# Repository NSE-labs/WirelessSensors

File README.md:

# WirelessSensors
 Development of wireless sensor hardware and software.

 Links to more information:

 [Project Overview](./Documentation/Wireless%20Sensor%20Project.md)

 [Project Checklist](./Documentation/Tasks.md)

 [CPU Board Rev A.1 Debugging](./Documentation/CPU%20board%20rev%20A.1%20debugging.md)

 [LoRa Board Rev A.1 Debugging](./Documentation/LoRa%20board%20rev%20A.1%20debugging.md)

 [LoRa Gateway Development](./Documentation/LoRa%20gateway%20development.md)

 [Range Testing](./Documentation/Range%20testing.md)

 [Sensor Module Architecture](./Documentation/Sensor%20module%20architecture.md)

 [CPU Board Rev B.2](./Documentation/CPU%20board%20rev%20B.2.md)

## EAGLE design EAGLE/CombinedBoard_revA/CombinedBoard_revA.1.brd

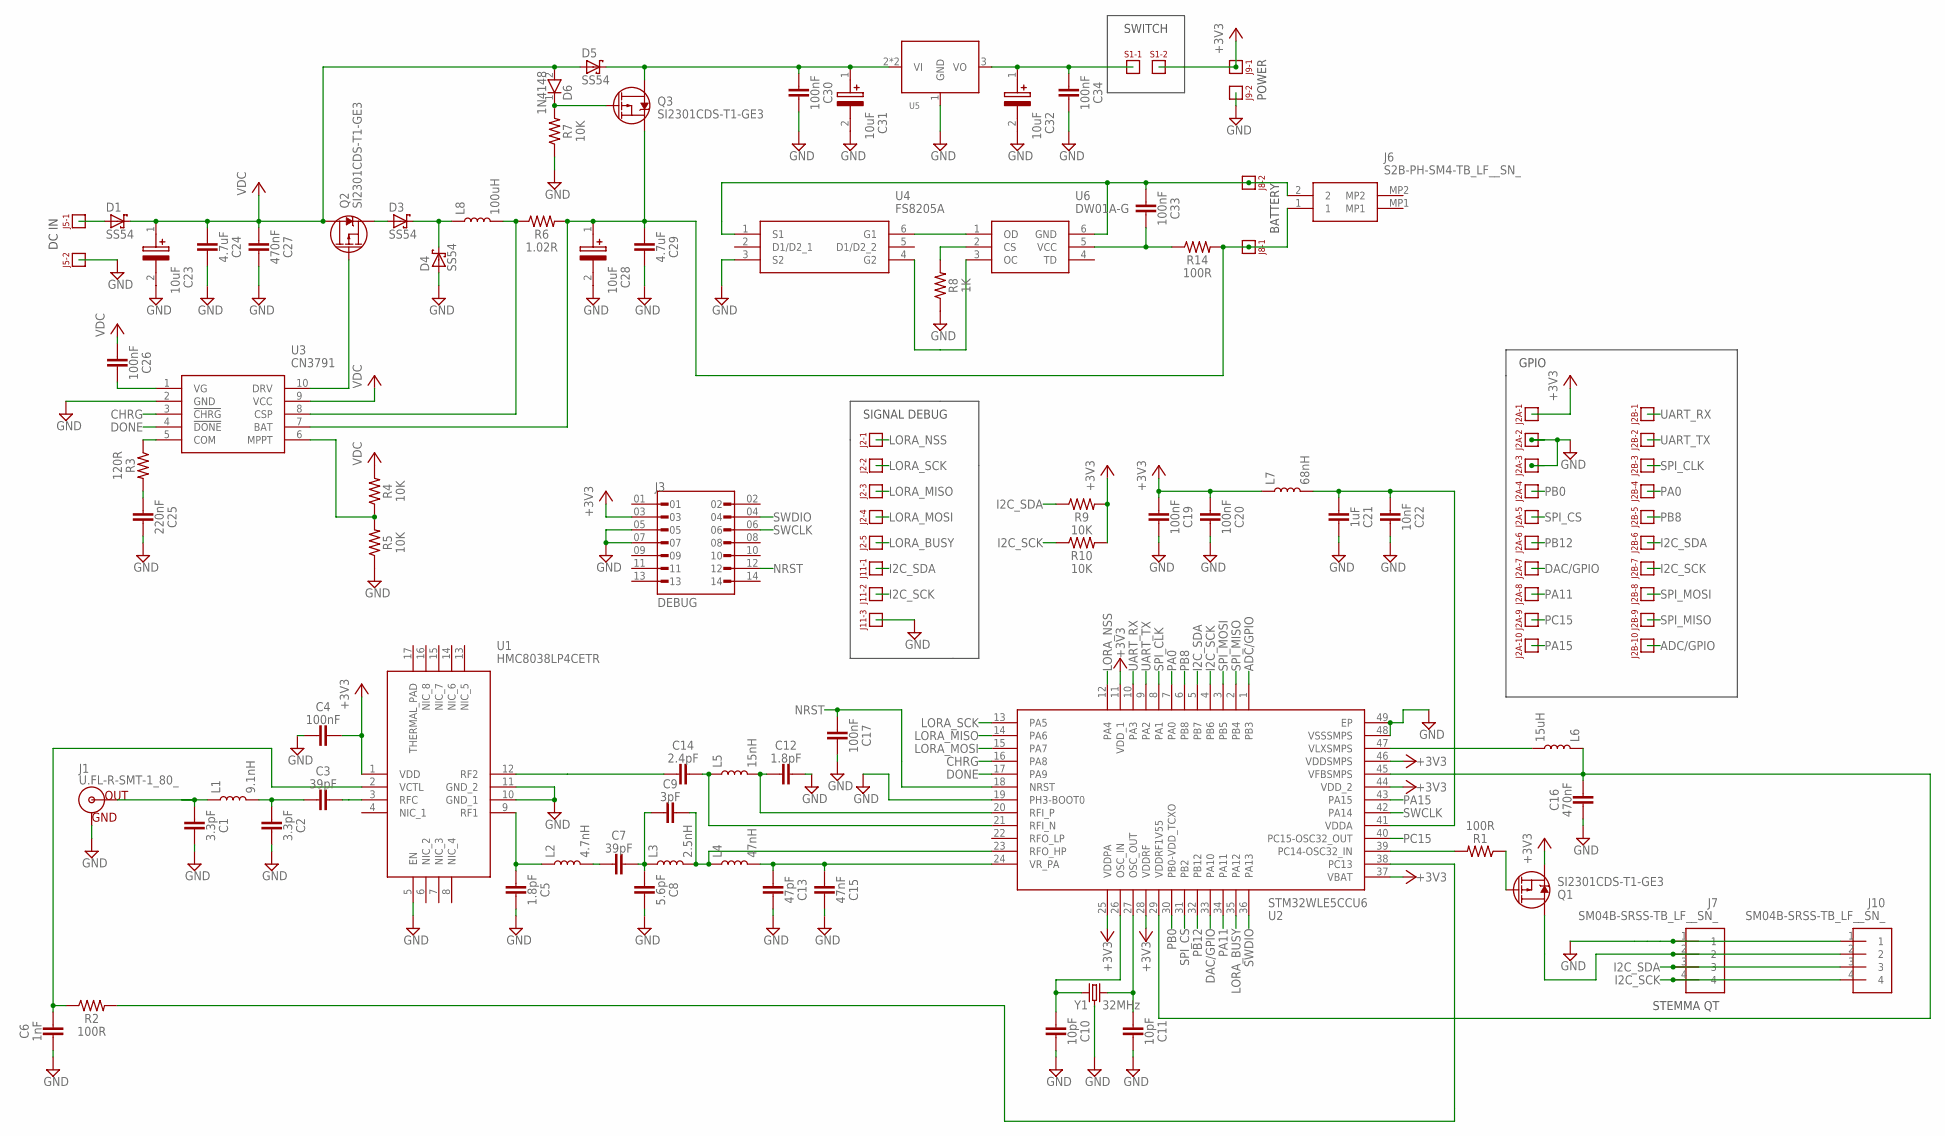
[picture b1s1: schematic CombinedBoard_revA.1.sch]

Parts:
C1, C2: 3.3pF; 0402
C3, C7: 39pF; 0402
C4, C17, C19, C20, C26, C30, C33, C34: 100nF; 0402
C5, C12: 1.8pF; 0402
C6: 1nF; 0603
C8: 5.6pF; 0402
C9: 3pF; 0603
C10, C11: 10pF; 0402
C13: 47pF; 0603
C14: 2.4pF; 0402
C15: 47nF; 0603
C16: 470nF; 0402
C21: 1uF; 0402
C22: 10nF; 0402
C23, C28, C31, C32: 10uF; 4MM_SMD_ECAP
C24, C29: 4.7uF; 1206
C25: 220nF; 0603
C27: 470nF; 0805
D1, D3, D4, D5: SS54; SMA(DO-214AC)
D6: 1N4148; SOD3716X135N
J1: U.FL-R-SMT-1_80_; UFLRSMT180
J2: HEADER_5PIN
J2A, J2B: HEADER_10PIN
J3: DEBUG; HEADER_DEBUG_SMD
J5: SOLAR; HEADER_2PIN
J6: S2B-PH-SM4-TB_LF__SN_; S2BPHSM4TBLFSN
J7, J10: SM04B-SRSS-TB_LF__SN_; SM04B-SRSS-TB(LFSN)
J8: BATTERY; HEADER_2PIN
J9: POWER; HEADER_2PIN
J11: HEADER_3PIN
L1: 9.1nH; 0402
L2: 4.7nH; 0402
L3: 2.5nH; 0402
L4: 47nH; 0603
L5: 15nH; 0402
L6: 15uH; 0805
L7: 68nH; 0603
L8: 100uH; L_SMD,7X7.8MM
Q1, Q2, Q3: SI2301CDS-T1-GE3; SOT-23
R1, R2, R14: 100R; 0402
R3: 120R; 0805
R4, R5, R7, R9, R10: 10K; 0402
R6: 1.02R; 1206
R8: 1K; 0402
S1: HEADER_2PIN
U1: HMC8038LP4CETR; QFN65P400X400X90-17N
U2: STM32WLE5CCU6; QFN50P700X700X60-49N
U3: CN3791; SOP100P600X175-10N
U4: FS8205A; SOT95P280X125-6N
U5: LDO_SOT89; SOT-89-3
U6: DW01A-G; SOT95P280X135-6N
Y1: 32MHz; SMD2016-4P

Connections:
+3V3: C4.2, C19.1, C20.1, J2A.P$1, J3.03, J9.P$1, L7.1, Q1.3 (S), R9.2, R10.2, S1.P$2, U1.1 (VDD), U2.11 (VDD_1), U2.25 (VDDPA), U2.28 (VDDRF), U2.37 (VBAT), U2.44 (VDD_2), U2.46 (VDDSMPS)
ADC/GPIO: J2B.P$10, U2.1 (PB3)
B+: C28.1 (+), C29.1, J6.1, J8.P$1, Q3.3 (S), R6.2, R14.2, U3.7 (BAT)
B-: C33.1, J6.2, J8.P$2, U4.1 (S1), U6.6 (GND)
CHRG: U2.16 (PA8), U3.3 (!CHRG)
DAC/GPIO: J2A.P$7, U2.33 (PA10)
DONE: U2.17 (PA9), U3.4 (!DONE)
GND: C1.2, C2.2, C4.1, C5.2, C6.1, C8.2, C10.2, C11.2, C12.2, C13.2, C15.2, C16.1, C17.2, C19.2, C20.2, C21.2, C22.2, C23.2 (-), C24.2, C25.2, C27.2, C28.2 (-), C29.2, C30.2, C31.2 (-), C32.2 (-), C34.2, D4.2 (A), J1.2 (GND), J1.3 (GND), J2A.P$2, J2A.P$3, J3.05, J3.07, J5.P$2, J7.1, J9.P$2, J10.1, J11.P$3, R5.1, R7.1, R8.1, U1.5 (EN), U1.10 (GND_1), U1.11 (GND_2), U2.19 (PH3-BOOT0), U2.48 (VSSSMPS), U2.49 (EP), U3.2 (GND), U4.3 (S2), U5.1 (GND), Y1.2 (3), Y1.4 (3)
I2C_SCK: J2B.P$7, J7.4, J10.4, J11.P$2, R10.1, U2.4 (PB6)
I2C_SDA: J2B.P$6, J7.3, J10.3, J11.P$1, R9.1, U2.5 (PB7)
LORA_BUSY: J2.P$5, U2.35 (PA12)
LORA_MISO: J2.P$3, U2.14 (PA6)
LORA_MOSI: J2.P$4, U2.15 (PA7)
LORA_NSS: J2.P$1, U2.12 (PA4)
LORA_SCK: J2.P$2, U2.13 (PA5)
unnamed: D3.2 (A), Q2.3 (S)
unnamed: C9.2, L3.2, L4.1, U2.23 (RFO_HP)
unnamed: C14.2, L5.1, U2.21 (RFI_N)
unnamed: L6.2, U2.47 (VLXSMPS)
unnamed: R2.2, U2.38 (PC13)
unnamed: D6.1 (K), Q3.1 (G), R7.2
unnamed: D1.2 (A), J5.P$1
unnamed: R1.2, U2.39 (PC14-OSC32_IN)
unnamed: Q1.1 (G), R1.1
unnamed: C32.1 (+), C34.1, S1.P$1, U5.3 (VO)
unnamed: J7.2, J10.2, Q1.2 (D)
unnamed: D3.1 (C), D4.1 (C), L8.P$1 (1)
unnamed: L8.P$2 (2), R6.1, U3.8 (CSP)
unnamed: C30.1, C31.1 (+), D5.1 (C), Q3.2 (D), U5.2 (VI), U5.4 (VI)
unnamed: Q2.1 (G), U3.10 (DRV)
unnamed: R3.1, U3.5 (COM)
unnamed: C25.1, R3.2
unnamed: C26.2, U3.1 (VG)
unnamed: R4.1, R5.2, U3.6 (MPPT)
unnamed: R8.2, U6.2 (CS)
unnamed: U4.4 (G2), U6.3 (OC)
unnamed: U4.6 (G1), U6.1 (OD)
unnamed: C33.2, R14.1, U6.5 (VCC)
unnamed: C1.1, J1.1 (OUT), L1.1
unnamed: C2.1, C3.1, L1.2
unnamed: C3.2, U1.3 (RFC)
unnamed: C6.2, R2.1, U1.2 (VCTL)
unnamed: C14.1, U1.12 (RF2)
unnamed: C5.1, L2.1, U1.9 (RF1)
unnamed: C7.1, L2.2
unnamed: C7.2, C8.1, C9.1, L3.1
NRST: C17.1, J3.12, U2.18 (NRST)
OSC_IN: C10.1, U2.26 (OSC_IN), Y1.1
OSC_OUT: C11.1, U2.27 (OSC_OUT), Y1.3 (2)
PA0: J2B.P$4, U2.7 (PA0)
PA11: J2A.P$8, U2.34 (PA11)
PA15: J2A.P$10, U2.43 (PA15)
PB0: J2A.P$4, U2.30 (PB0-VDD_TCXO)
PB8: J2B.P$5, U2.6 (PB8)
PB12: J2A.P$6, U2.32 (PB12)
PC15: J2A.P$9, U2.40 (PC15-OSC32_OUT)
RFI_3: C12.1, L5.2, U2.20 (RFI_P)
SPI_CLK: J2B.P$3, U2.8 (PA1)
SPI_CS: J2A.P$5, U2.31 (PB2)
SPI_MISO: J2B.P$9, U2.2 (PB4)
SPI_MOSI: J2B.P$8, U2.3 (PB5)
SWCLK: J3.06, U2.42 (PA14)
SWDIO: J3.04, U2.36 (PA13)
UART_RX: J2B.P$1, U2.10 (PA3)
UART_TX: J2B.P$2, U2.9 (PA2)
VDC: C23.1 (+), C24.1, C26.1, C27.1, D1.1 (C), D5.2 (A), D6.2 (A), Q2.2 (D), R4.2, U3.9 (VCC)
VDDA: C21.1, C22.1, L7.2, U2.41 (VDDA)
VREG1: C16.2, L6.1, U2.29 (VDDRF1V55), U2.45 (VFBSMPS)
VR_PA1: C13.1, C15.1, L4.2, U2.24 (VR_PA)

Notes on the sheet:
GPIO
SIGNAL DEBUG
SWITCH
POWER
BATTERY
DC IN
STEMMA QT

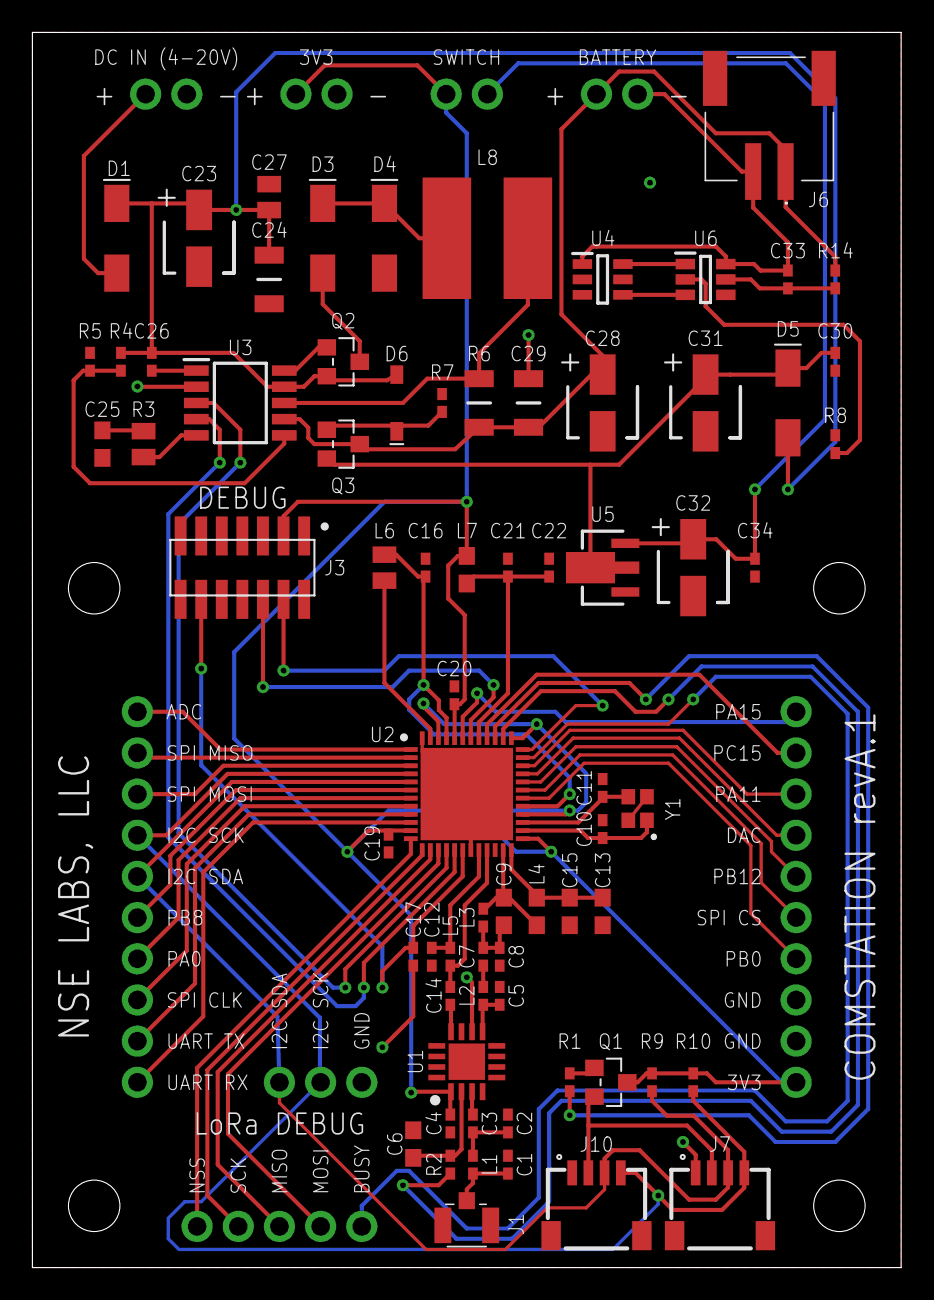
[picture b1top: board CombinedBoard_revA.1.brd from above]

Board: 2 copper layers, 53.6 x 76.2 mm, 80 parts (0 on the bottom side), 69 nets.

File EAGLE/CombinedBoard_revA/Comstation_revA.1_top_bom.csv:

Comment,Designator,Footprint,LCSC Part #
1.02R,R9 R10 U5 R6,1206,
1.8pF,C5 C12,0402,
1K,R8,0402,
1N4148,D6,SOD3716X135N,
1nF,C6,0603,
1uF,C21,0402,
2.4pF,C14,0402,
2.5nH,L3,0402,
3.3pF,C1 C2,0402,
3pF,C9,0603,
4.7nH,L2,0402,
4.7uF,C24 C29,1206,
5.6pF,C8,0402,
9.1nH,L1,0402,
10K,R4 R5 R7,0402,
10nF,C22,0402,
10pF,C10 C11,0402,
10uF,C23 C28 C31 C32,4MM_SMD_ECAP,
15nH,L5,0402,
15uH,L6,0805,
32MHz,Y1,SMD3225-4P,
39pF,C3 C7,0402,
47nF,C15,0603,
47nH,L4,0603,
47pF,C13,0603,
68nH,L7,0603,
100R,R1 R2 R14,0402,
100nF,C4 C17 C19 C20 C26 C30 C33 C34,0402,
100uH,L8,L_SMD 7X7.8MM,
120R,R3,0805,
220nF,C25,0603,
470nF,C16,0402,
470nF,C27,0805,
CN3791,U3,SOP100P600X175-10N,
DEBUG,J3,HEADER_DEBUG_SMD,
DW01A-G,U6,SOT95P280X135-6N,
FS8205A,U4,SOT95P280X125-6N,
HMC8038LP4CETR,U1,QFN65P400X400X90-17N,
S2B-PH-SM4-TB_LF__SN_,J6,S2BPHSM4TBLFSN,
SI2301CDS-T1-GE3,Q1 Q2 Q3,SOT-23,
SM04B-SRSS-TB_LF__SN_,J7 J10,SM04B-SRSS-TB(LFSN),
SS54,D1 D3 D4 D5,SMA(DO-214AC),
STM32WLE5CCU6,U2,QFN50P700X700X60-49N,
U.FL-R-SMT-1_80_,J1,UFLRSMT180,

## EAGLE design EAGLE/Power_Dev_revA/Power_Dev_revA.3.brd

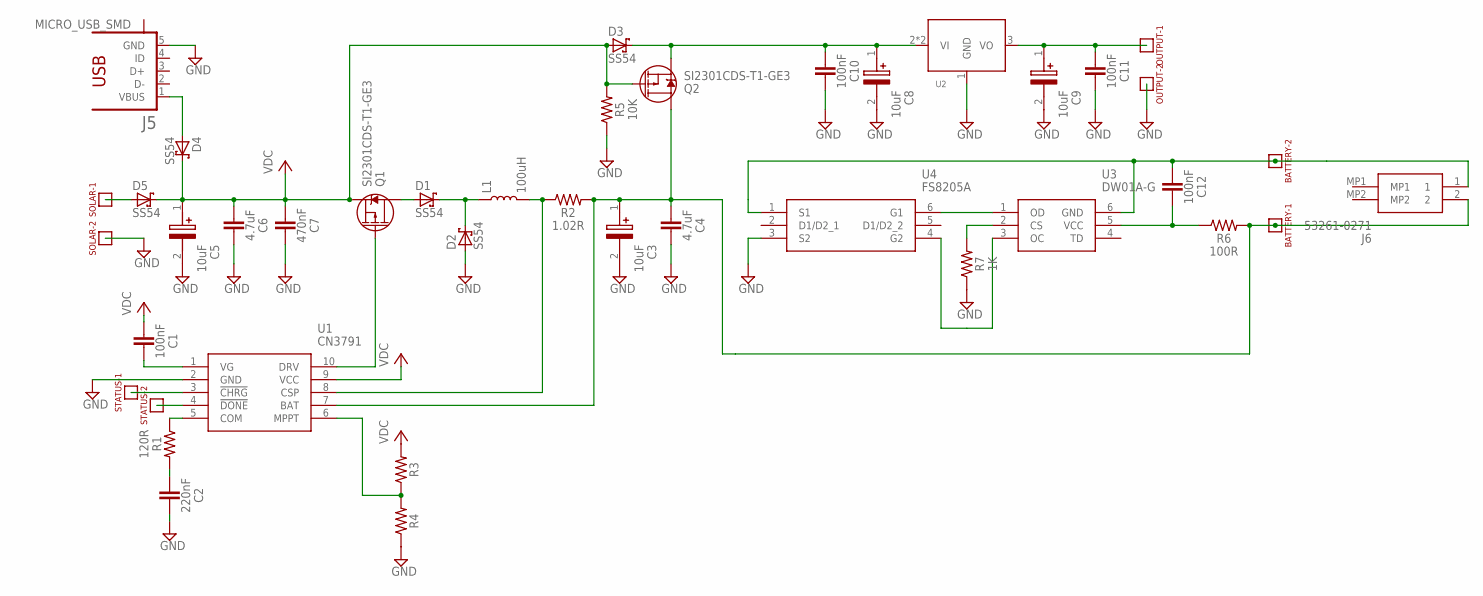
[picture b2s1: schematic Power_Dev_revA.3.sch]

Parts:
BATTERY: HEADER_2PIN
C1, C10, C11, C12: 100nF; 0402
C2: 220nF; 0603
C3, C5, C8, C9: 10uF; 6MM_SMD_ECAP
C4, C6: 4.7uF; 1206
C7: 470nF; 0805
D1, D2, D3, D4, D5: SS54; SMA(DO-214AC)
J5: MICRO_USB_SMD; 10118192-0002LF
J6: 53261-0271; 532610271
L1: 100uH; L_SMD,7X7.8MM
OUTPUT: HEADER_2PIN
Q1, Q2: SI2301CDS-T1-GE3; SOT-23
R1: 120R; 0805
R2: 1.02R; 1206
R3, R4: RESISTOR_TH
R5: 10K; 0402
R6: 100R; 0402
R7: 1K; 0402
SOLAR: HEADER_2PIN
STATUS: HEADER_2PIN
U1: CN3791; SOP100P600X175-10N
U2: LDO_SOT89; SOT-89-3
U3: DW01A-G; SOT95P280X135-6N
U4: FS8205A; SOT95P280X125-6N

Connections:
GND: C2.2, C3.2 (-), C4.2, C5.2 (-), C6.2, C7.2, C8.2 (-), C9.2 (-), C10.2, C11.2, D2.2 (A), J5.5 (GND), OUTPUT.P$2, R4.P$1 (1), R5.1, R7.1, SOLAR.P$2, U1.2 (GND), U2.1 (GND), U4.3 (S2)
unnamed: D4.2 (A), J5.1 (VBUS)
unnamed: D5.2 (A), SOLAR.P$1
unnamed: D1.2 (A), Q1.3 (D)
unnamed: D1.1 (C), D2.1 (C), L1.P$1 (1)
unnamed: L1.P$2 (2), R2.1, U1.8 (CSP)
unnamed: C9.1 (+), C11.1, OUTPUT.P$1, U2.3 (VO)
unnamed: Q1.1 (G), U1.10 (DRV)
unnamed: C8.1 (+), C10.1, D3.1 (C), Q2.2 (S), U2.2 (VI), U2.4 (VI)
unnamed: R1.1, U1.5 (COM)
unnamed: C2.1, R1.2
unnamed: STATUS.P$1, U1.3 (!CHRG)
unnamed: STATUS.P$2, U1.4 (!DONE)
unnamed: C1.2, U1.1 (VG)
unnamed: R3.P$1 (1), R4.P$2 (2), U1.6 (MPPT)
unnamed: R7.2, U3.2 (CS)
unnamed: U3.3 (OC), U4.4 (G2)
unnamed: U3.1 (OD), U4.6 (G1)
unnamed: BATTERY.P$2, C12.1, J6.1, U3.6 (GND), U4.1 (S1)
unnamed: C12.2, R6.1, U3.5 (VCC)
unnamed: BATTERY.P$1, C3.1 (+), C4.1, J6.2, Q2.3 (D), R2.2, R6.2, U1.7 (BAT)
VDC: C1.1, C5.1 (+), C6.1, C7.1, D3.2 (A), D4.1 (C), D5.1 (C), Q1.2 (S), Q2.1 (G), R3.P$2 (2), R5.2, U1.9 (VCC)

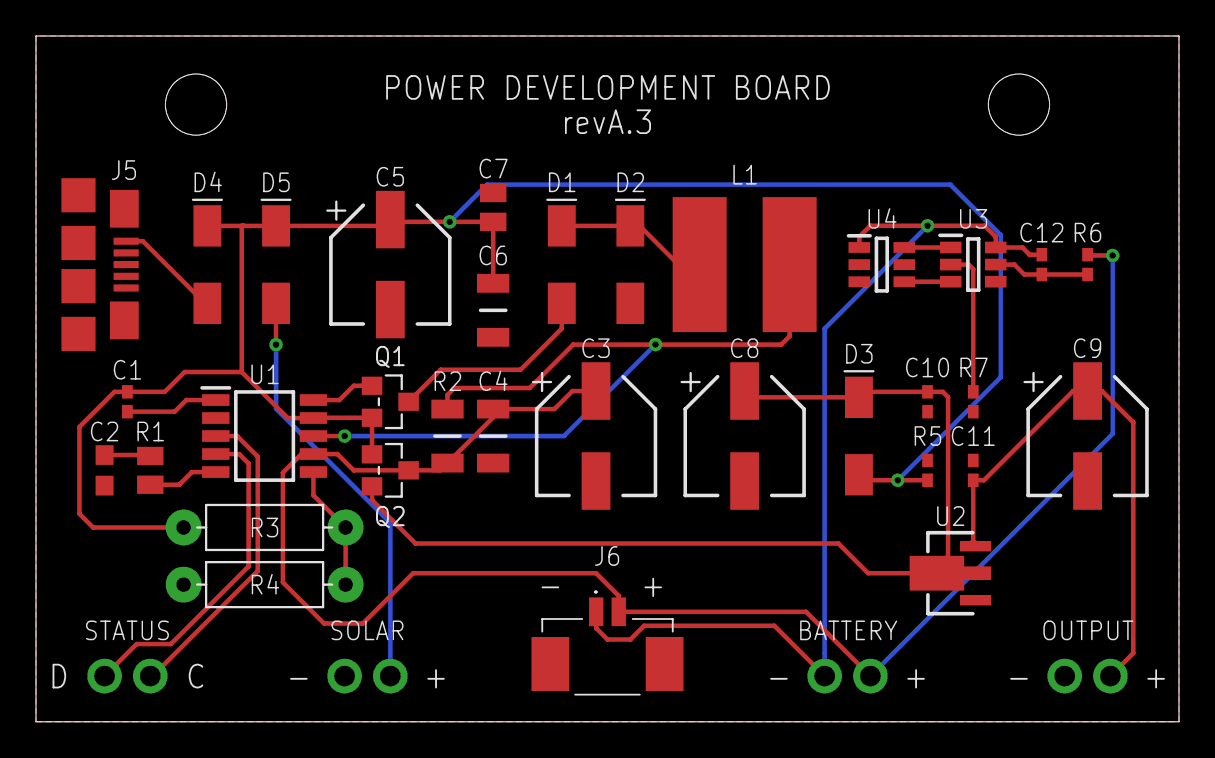
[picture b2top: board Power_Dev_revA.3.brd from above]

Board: 2 copper layers, 63.5 x 38.1 mm, 37 parts (0 on the bottom side), 22 nets.

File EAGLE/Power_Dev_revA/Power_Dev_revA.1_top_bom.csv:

Comment,Designator,Footprint,LCSC Part #
100nF 50V,C1 C10 C11 C12,0402,C307331
220 nF 25V,C2,0603,C21120
10 uF Electrolytic 100V,C3 C5 C8 C9,"SMD,D6.3xL7.7mm",C72482
4.7uF 50V,C4 C6,1206,C29823 
470 nF 50V,C7,0805,C13967
SS54 Diode 40V 5A,D1 D2 D3 D4 D5,SMA(DO-214AC),C22452
MICRO_USB_SMD,J5,10118192-0002LF,C2972784
100uH 730 mA,L1,"SMD,7x7.8mm ",C2929443 
120 ohm,R1,0805,C17437
1.02 ohm,R2,1206,C323217
10K,R5,0402,C25744
100 ohm,R6,0402,C25076
1K,R7,0402,C11702
SI2301CDS-T1-GE3 20V,Q1 Q2,SOT-23,C10487
CN3791,U1,SSOP-10-150mil,C154992
HT7333-1,U2,SOT-89-3,C77777
DW01A,U3,SOT-23-6L,C351410
FS8205A,U4,SOT-23-6L,C908265

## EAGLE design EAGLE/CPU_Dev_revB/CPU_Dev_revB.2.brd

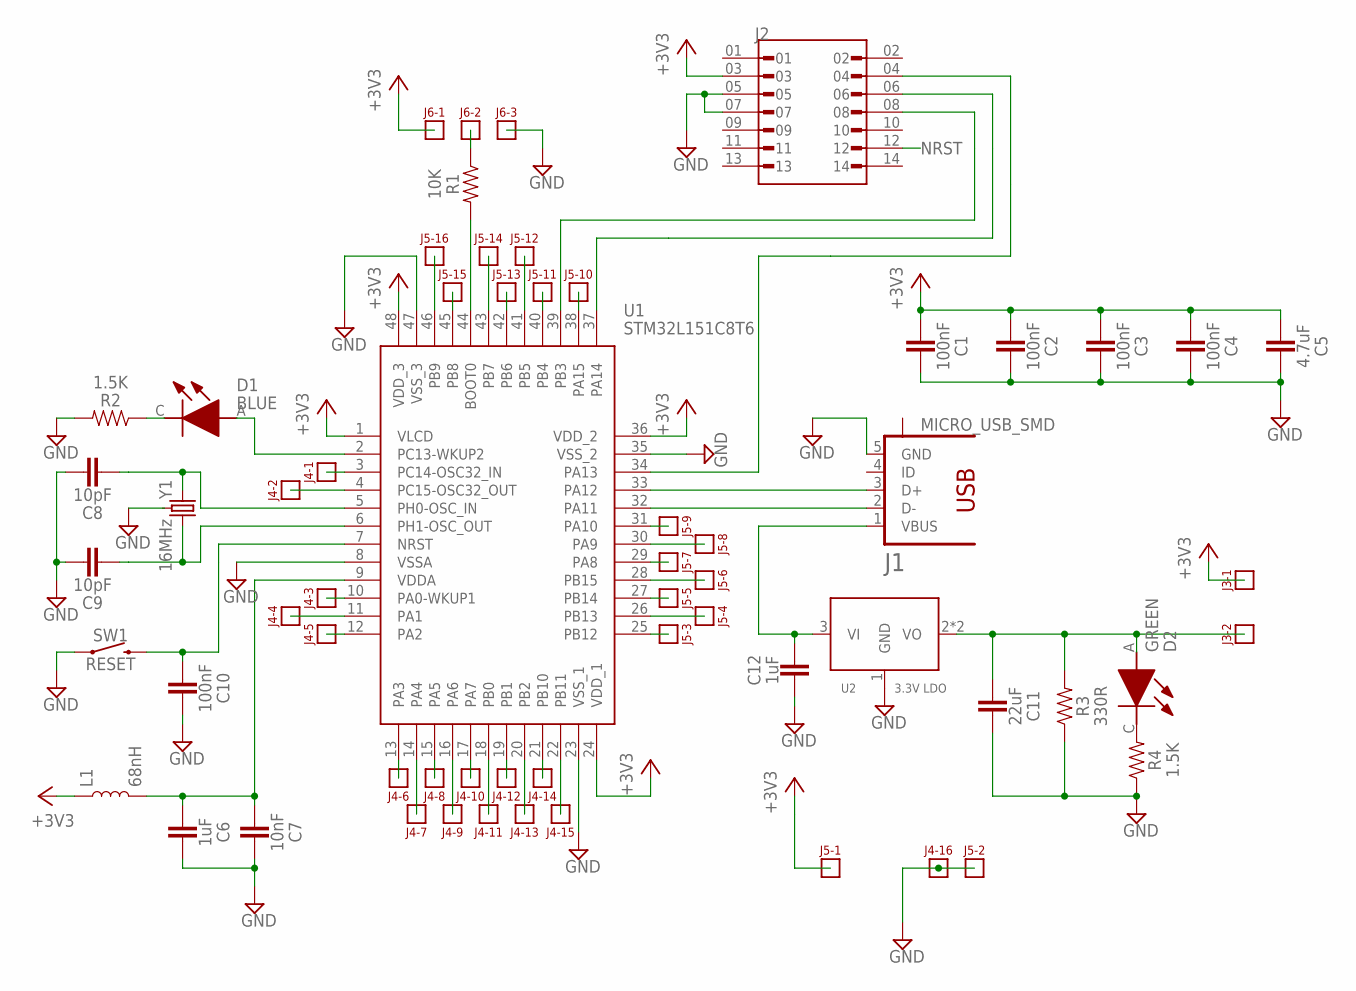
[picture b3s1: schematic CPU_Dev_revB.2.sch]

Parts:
C1, C2, C3, C4, C10: 100nF; 0402
C5: 4.7uF; 0402
C6, C12: 1uF; 0402
C7: 10nF; 0402
C8, C9: 10pF; 0402
C11: 22uF; 1206
D1: BLUE; LED_0603
D2: GREEN; LED_0603
J1: MICRO_USB_SMD; 10118192-0002LF
J2: HEADER_DEBUG_SMD
J3: HEADER_2PIN
J4, J5: HEADER_16PIN
J6: HEADER_3PIN
L1: 68nH; 0603
R1: 10K; 0402
R2, R4: 1.5K; 0402
R3: 330R; 0402
SW1: RESET; PUSHBUTTON_SMD
U1: STM32L151C8T6; LQFP-48_7X7
U2: 3.3V LDO; SOT223
Y1: 16MHz; SMD3225-4P

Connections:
+3V3: C1.1, C2.1, C3.1, C4.1, C5.1, J2.03, J3.P$1, J5.P$1, J6.P$1, L1.1, U1.1 (VLCD), U1.24 (VDD_1), U1.36 (VDD_2), U1.48 (VDD_3)
BOOT0: R1.2, U1.44 (BOOT0)
GND: C1.2, C2.2, C3.2, C4.2, C5.2, C6.2, C7.2, C8.2, C9.2, C10.2, C11.2, C12.1, J1.5 (GND), J2.05, J2.07, J4.P$16, J5.P$2, J6.P$3, R2.2, R3.1, R4.1, SW1.A1 (1), SW1.B1 (1), U1.8 (VSSA), U1.23 (VSS_1), U1.35 (VSS_2), U1.47 (VSS_3), U2.1 (GND), Y1.2 (3), Y1.4 (3)
unnamed: C12.2, J1.1 (VBUS), U2.3 (VI)
unnamed: C11.1, D2.A, J3.P$2, R3.2, U2.2 (VO), U2.4 (VO)
unnamed: D2.C (K), R4.2
unnamed: D1.C (K), R2.1
unnamed: J6.P$2, R1.1
NRST: C10.1, J2.12, SW1.C1 (2), SW1.D1 (2), U1.7 (NRST)
PA0: J4.P$3, U1.10 (PA0-WKUP1)
PA1: J4.P$4, U1.11 (PA1)
PA2: J4.P$5, U1.12 (PA2)
PA3: J4.P$6, U1.13 (PA3)
PA4: J4.P$7, U1.14 (PA4)
PA5: J4.P$8, U1.15 (PA5)
PA6: J4.P$9, U1.16 (PA6)
PA7: J4.P$10, U1.17 (PA7)
PA8: J5.P$7, U1.29 (PA8)
PA9: J5.P$8, U1.30 (PA9)
PA10: J5.P$9, U1.31 (PA10)
PA11: J1.2 (D-), U1.32 (PA11)
PA12: J1.3 (D+), U1.33 (PA12)
PA13: J2.04, U1.34 (PA13)
PA14: J2.06, U1.37 (PA14)
PA15: J5.P$10, U1.38 (PA15)
PB0: J4.P$11, U1.18 (PB0)
PB1: J4.P$12, U1.19 (PB1)
PB2: J4.P$13, U1.20 (PB2)
PB3: J2.08, U1.39 (PB3)
PB4: J5.P$11, U1.40 (PB4)
PB5: J5.P$12, U1.41 (PB5)
PB6: J5.P$13, U1.42 (PB6)
PB7: J5.P$14, U1.43 (PB7)
PB8: J5.P$15, U1.45 (PB8)
PB9: J5.P$16, U1.46 (PB9)
PB10: J4.P$14, U1.21 (PB10)
PB11: J4.P$15, U1.22 (PB11)
PB12: J5.P$3, U1.25 (PB12)
PB13: J5.P$4, U1.26 (PB13)
PB14: J5.P$5, U1.27 (PB14)
PB15: J5.P$6, U1.28 (PB15)
PC14: J4.P$1, U1.3 (PC14-OSC32_IN)
PC15: J4.P$2, U1.4 (PC15-OSC32_OUT)
PH0: C8.1, U1.5 (PH0-OSC_IN), Y1.1
PH1: C9.1, U1.6 (PH1-OSC_OUT), Y1.3 (2)
VDDA: C6.1, C7.1, L1.2, U1.9 (VDDA)
WKUP: D1.A, U1.2 (PC13-WKUP2)

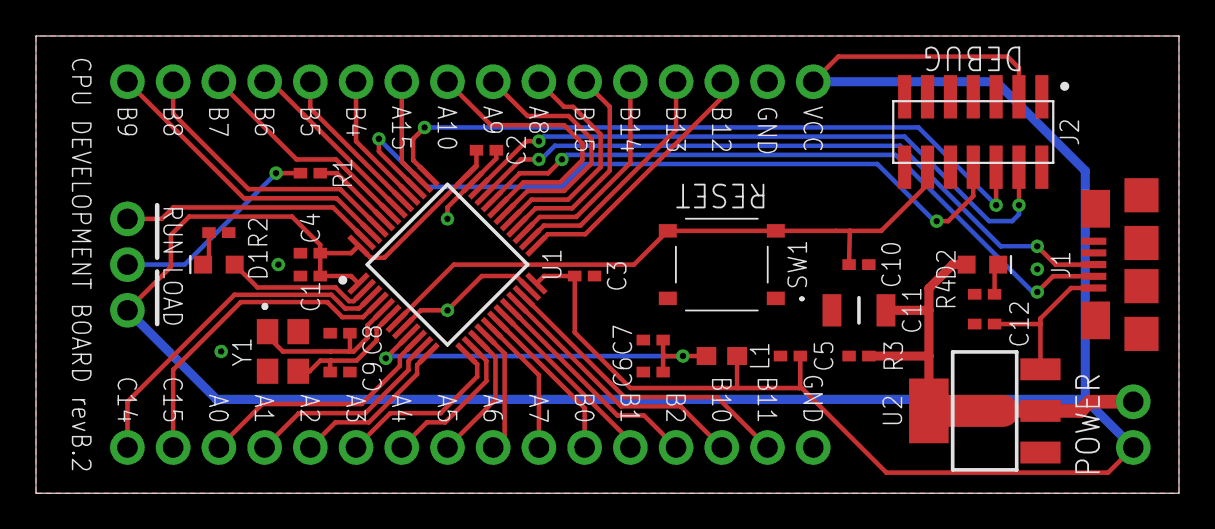
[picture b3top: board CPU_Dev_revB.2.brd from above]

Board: 2 copper layers, 63.5 x 25.4 mm, 29 parts (0 on the bottom side), 47 nets.

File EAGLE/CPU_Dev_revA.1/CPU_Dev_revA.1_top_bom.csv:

Comment,Designator,Footprint,LCSC Part #
1.5K,R2 R4,0402,
1uF,C6 C12,0402,
3.3V LDO,U2,SOT223,
4.7uF,C5,0402,
10K,R1,0402,
10nF,C7,0402,
10pF,C8 C9,0402,
16MHz,Y1,SMD3225-4P,
22uF,C11,1206,
68nH,L1,0603,
100nF,C1 C2 C3 C4 C10,0402,
330R,R3,0402,
BLUE,D1,LED_0603,
GREEN,D2,LED_0603,
MICRO_USB_SMD,J1,10118192-0002LF,
RESET,SW1,PUSHBUTTON_SMD,
STM32L151C8T6,U1,LQFP-48_7X7,

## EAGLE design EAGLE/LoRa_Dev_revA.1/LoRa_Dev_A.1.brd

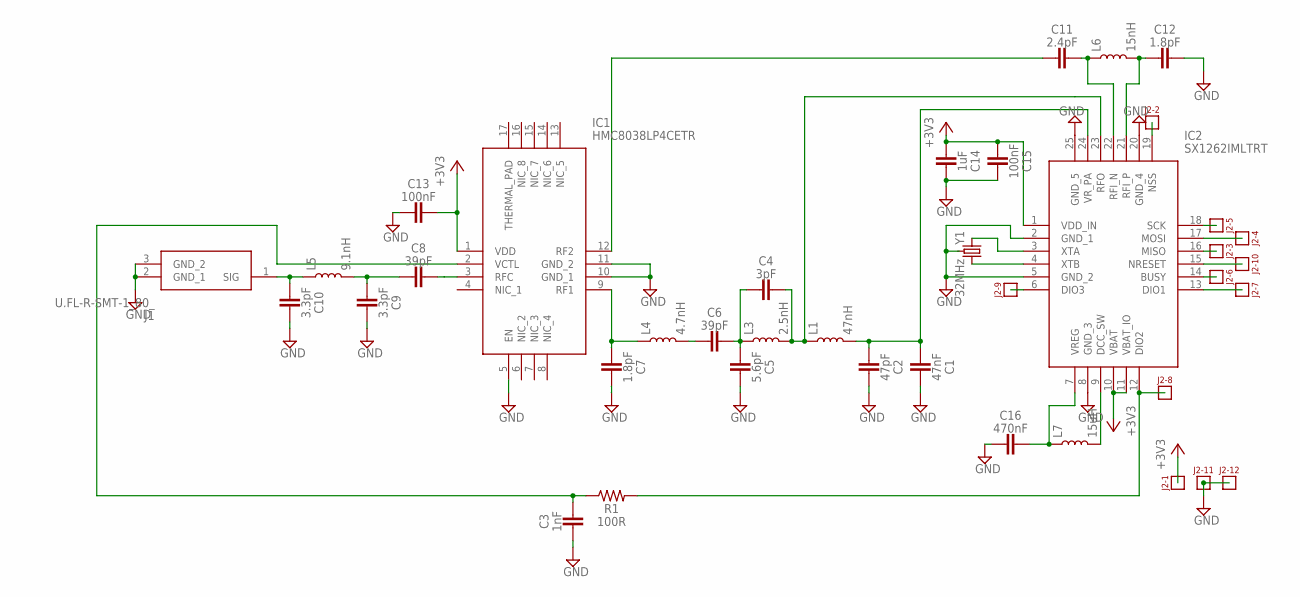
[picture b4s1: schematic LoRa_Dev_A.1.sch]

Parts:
C1: 47nF; 0603
C2: 47pF; 0603
C3: 1nF; 0603
C4: 3pF; 0603
C5: 5.6pF; 0402
C6, C8: 39pF; 0402
C7, C12: 1.8pF; 0402
C9, C10: 3.3pF; 0402
C11: 2.4pF; 0402
C13, C15: 100nF; 0402
C14: 1uF; 0402
C16: 470nF; 0402
IC1: HMC8038LP4CETR; QFN65P400X400X90-17N
IC2: SX1262IMLTRT; QFN50P400X400X100-25N
J1: U.FL-R-SMT-1_80_; UFLRSMT180
J2: HEADER_12PIN
L1: 47nH; 0603
L3: 2.5nH; 0402
L4: 4.7nH; 0402
L5: 9.1nH; 0402
L6: 15nH; 0402
L7: 15uH; 0805
R1: 100R; 0402
Y1: 32MHz; SMD2016-4P

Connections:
+3V3: C13.2, C14.1, C15.1, IC1.1 (VDD), IC2.1 (VDD_IN), IC2.10 (VBAT), IC2.11 (VBAT_IO), J2.P$1
BUSY: IC2.14 (BUSY), J2.P$6
DCC_SW: IC2.9 (DCC_SW), L7.2
DIO1: IC2.13 (DIO1), J2.P$7
DIO2: IC2.12 (DIO2), J2.P$8, R1.2
DIO3: IC2.6 (DIO3), J2.P$9
GND: C1.2, C2.2, C3.1, C5.2, C7.2, C9.2, C10.2, C12.2, C13.1, C14.2, C15.2, C16.1, IC1.5 (EN), IC1.10 (GND_1), IC1.11 (GND_2), IC2.2 (GND_1), IC2.5 (GND_2), IC2.8 (GND_3), IC2.20 (GND_4), IC2.25 (GND_5), J1.2 (GND_1), J1.3 (GND_2), J2.P$11, J2.P$12, Y1.2 (3), Y1.4 (3)
MISO: IC2.16 (MISO), J2.P$3
MOSI: IC2.17 (MOSI), J2.P$4
unnamed: C10.1, J1.1 (SIG), L5.1
unnamed: C8.1, C9.1, L5.2
unnamed: C8.2, IC1.3 (RFC)
unnamed: C3.2, IC1.2 (VCTL), R1.1
unnamed: C11.1, IC1.12 (RF2)
unnamed: C7.1, IC1.9 (RF1), L4.1
unnamed: C6.1, L4.2
unnamed: C4.1, C5.1, C6.2, L3.1
NRESET: IC2.15 (NRESET), J2.P$10
NSS: IC2.19 (NSS), J2.P$2
RFI_1: C11.2, IC2.22 (RFI_N), L6.1
RFI_2: C12.1, IC2.21 (RFI_P), L6.2
RFO: C4.2, IC2.23 (RFO), L1.1, L3.2
SCK: IC2.18 (SCK), J2.P$5
VREG: C16.2, IC2.7 (VREG), L7.1
VR_PA: C1.1, C2.1, IC2.24 (VR_PA), L1.2
XTA: IC2.3 (XTA), Y1.1
XTB: IC2.4 (XTB), Y1.3 (2)

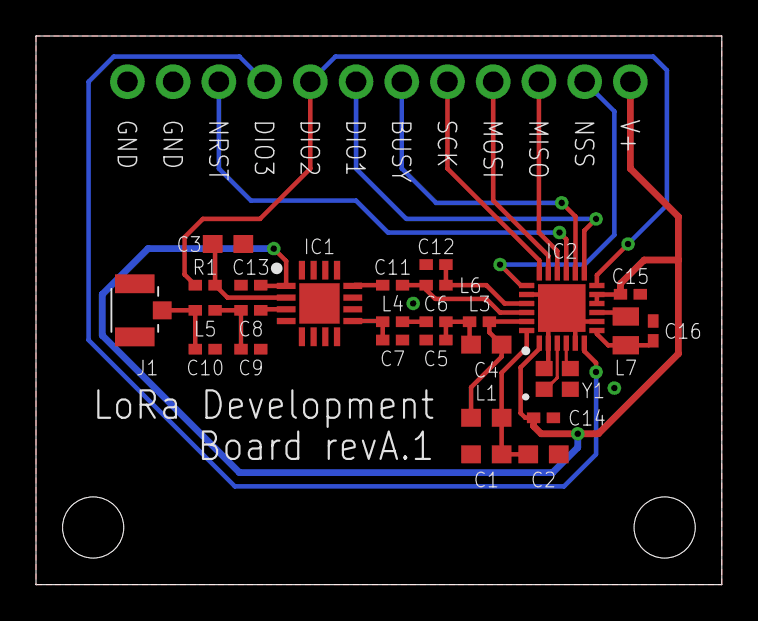
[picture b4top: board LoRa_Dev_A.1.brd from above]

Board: 2 copper layers, 38.1 x 30.5 mm, 28 parts (0 on the bottom side), 27 nets.

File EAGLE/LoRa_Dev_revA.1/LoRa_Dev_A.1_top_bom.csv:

Comment,Designator,Footprint,LCSC Part #
1.8pF,C7 C12,0402,
1nF,C3,0603,
1uF,C14,0402,
2.4pF,C11,0402,
2.5nH,L3,0402,
3.3pF,C9 C10,0402,
3pF,C4,0603,
4.7nH,L4,0402,
5.6pF,C5,0402,
9.1nH,L5,0402,
15nH,L6,0402,
15uH,L7,0805,
32MHz,Y1,SMD2016-4P,
39pF,C6 C8,0402,
47nF,C1,0603,
47nH,L1,0603,
47pF,C2,0603,
100R,R1,0402,
100nF,C13 C15,0402,
470nF,C16,0402,
HMC8038LP4CETR,IC1,QFN65P400X400X90-17N,
SX1262IMLTRT,IC2,QFN50P400X400X100-25N,
U.FL-R-SMT-1_80_,J1,UFLRSMT180,

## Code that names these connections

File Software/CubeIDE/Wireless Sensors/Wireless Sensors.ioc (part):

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Mcu.Name=STM32L151C(6-8-B)Tx
Mcu.Package=LQFP48
Mcu.UserName=STM32L151C8Tx
PA0-WKUP1.GPIOParameters=GPIO_Label
PA0-WKUP1.GPIO_Label=LoRa_NRST
PA0-WKUP1.Signal=GPIO_Output
PA1.GPIOParameters=GPIO_Label
PA1.GPIO_Label=LoRa_DIO3
PA1.Signal=GPIO_Input
PA10.GPIOParameters=GPIO_Label
PA10.GPIO_Label=ID_CS
PA10.Signal=GPIO_Output
PA11.Mode=Device
PA11.Signal=USB_DM
PA12.Mode=Device
PA12.Signal=USB_DP
PA13.Mode=Trace_Asynchronous_SW
PA13.Signal=SYS_JTMS-SWDIO
PA14.Mode=Trace_Asynchronous_SW
PA14.Signal=SYS_JTCK-SWCLK
PA2.GPIOParameters=GPIO_Label
PA2.GPIO_Label=LoRa_DIO2
PA2.Signal=GPIO_Input
PA3.GPIOParameters=GPIO_Label
PA3.GPIO_Label=LoRa_DIO1
PA3.Signal=GPIO_Input
PA4.GPIOParameters=GPIO_Label
PA4.GPIO_Label=LoRa_NSS
PA4.Signal=GPIO_Output
PA5.Mode=Full_Duplex_Master
PA5.Signal=SPI1_SCK
PA6.Mode=Full_Duplex_Master
PA6.Signal=SPI1_MISO
PA7.Mode=Full_Duplex_Master
PA7.Signal=SPI1_MOSI
PA8.GPIOParameters=GPIO_Label
PA8.GPIO_Label=LoRa_BUSY
PA8.Signal=GPIO_Input
PA9.GPIOParameters=GPIO_Label
PA9.GPIO_Label=ID_PL
PA9.Signal=GPIO_Output
PB10.GPIOParameters=GPIO_Label
PB10.GPIO_Label=OneWire
PB10.Signal=GPIO_Output
PB3.Mode=Trace_Asynchronous_SW
PB3.Signal=SYS_JTDO-TRACESWO
PB6.Mode=I2C
PB6.Signal=I2C1_SCL
PB7.Mode=I2C
PB7.Signal=I2C1_SDA
PC13-WKUP2.GPIOParameters=GPIO_Label
PC13-WKUP2.GPIO_Label=LED
PC13-WKUP2.Signal=GPIO_Output
PH0-OSC_IN.Mode=HSE-External-Oscillator
PH0-OSC_IN.Signal=RCC_OSC_IN
PH1-OSC_OUT.Mode=HSE-External-Oscillator
PH1-OSC_OUT.Signal=RCC_OSC_OUT
RCC.HSE_VALUE=16000000
RCC.SYSCLKFreq_VALUE=16000000
RCC.SYSCLKSource=RCC_SYSCLKSOURCE_HSI
board=custom

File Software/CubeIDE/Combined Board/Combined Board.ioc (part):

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Mcu.Name=STM32WLE5CCUx
Mcu.Package=UFQFPN48
Mcu.UserName=STM32WLE5CCUx
PA1.Mode=Full_Duplex_Master
PA1.Signal=SPI1_SCK
PA10.Signal=COMP_DAC1_group
PA12.Mode=RF-BUSY
PA12.Signal=DEBUG_RF-BUSY
PA13.Mode=Serial_Wire
PA13.Signal=DEBUG_JTMS-SWDIO
PA14.Mode=Serial_Wire
PA14.Signal=DEBUG_JTCK-SWCLK
PA2.Mode=Asynchronous
PA2.Signal=LPUART1_TX
PA3.Mode=Asynchronous
PA3.Signal=LPUART1_RX
PA4.Mode=SUBGHZSPI-Monitoring
PA4.Signal=DEBUG_SUBGHZSPI-NSSOUT
PA5.Mode=SUBGHZSPI-Monitoring
PA5.Signal=DEBUG_SUBGHZSPI-SCKOUT
PA6.Mode=SUBGHZSPI-Monitoring
PA6.Signal=DEBUG_SUBGHZSPI-MISOOUT
PA7.Mode=SUBGHZSPI-Monitoring
PA7.Signal=DEBUG_SUBGHZSPI-MOSIOUT
PB2.Mode=NSS_Signal_Hard_Output
PB2.Signal=SPI1_NSS
PB3.Mode=IN2
PB3.Signal=ADC_IN2
PB4.Mode=Full_Duplex_Master
PB4.Signal=SPI1_MISO
PB5.Mode=Full_Duplex_Master
PB5.Signal=SPI1_MOSI
PB6.Mode=I2C
PB6.Signal=I2C1_SCL
PB7.Mode=I2C
PB7.Signal=I2C1_SDA
RCC.HSE_VALUE=8000000
board=custom

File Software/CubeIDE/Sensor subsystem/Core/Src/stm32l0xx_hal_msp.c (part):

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    __HAL_RCC_ADC1_CLK_ENABLE();

    __HAL_RCC_GPIOA_CLK_ENABLE();
    /**ADC GPIO Configuration
    PA0     ------> ADC_IN0
    */
    GPIO_InitStruct.Pin = GPIO_PIN_0;
    GPIO_InitStruct.Mode = GPIO_MODE_ANALOG;
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    /* Peripheral clock disable */
    __HAL_RCC_ADC1_CLK_DISABLE();

    /**ADC GPIO Configuration
    PA0     ------> ADC_IN0
    */
    HAL_GPIO_DeInit(GPIOA, GPIO_PIN_0);

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  /* USER CODE END I2C1_MspInit 0 */

    __HAL_RCC_GPIOA_CLK_ENABLE();
    /**I2C1 GPIO Configuration
    PA9     ------> I2C1_SCL
    PA10     ------> I2C1_SDA
    */
    GPIO_InitStruct.Pin = GPIO_PIN_9|GPIO_PIN_10;
    GPIO_InitStruct.Mode = GPIO_MODE_AF_OD;
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  /* USER CODE END I2C2_MspInit 0 */

    __HAL_RCC_GPIOB_CLK_ENABLE();
    /**I2C2 GPIO Configuration
    PB10     ------> I2C2_SCL
    PB11     ------> I2C2_SDA
    */
    GPIO_InitStruct.Pin = GPIO_PIN_10|GPIO_PIN_11;
    GPIO_InitStruct.Mode = GPIO_MODE_AF_OD;
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
    __HAL_RCC_GPIOA_CLK_ENABLE();
    __HAL_RCC_GPIOB_CLK_ENABLE();
    /**I2C3 GPIO Configuration
    PA8     ------> I2C3_SCL
    PB4     ------> I2C3_SDA
    */
    GPIO_InitStruct.Pin = GPIO_PIN_8;
    GPIO_InitStruct.Mode = GPIO_MODE_AF_OD;
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    /* Peripheral clock disable */
    __HAL_RCC_I2C1_CLK_DISABLE();

    /**I2C1 GPIO Configuration
    PA9     ------> I2C1_SCL
    PA10     ------> I2C1_SDA
    */
    HAL_GPIO_DeInit(GPIOA, GPIO_PIN_9);

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    /* Peripheral clock disable */
    __HAL_RCC_I2C2_CLK_DISABLE();

    /**I2C2 GPIO Configuration
    PB10     ------> I2C2_SCL
    PB11     ------> I2C2_SDA
    */
    HAL_GPIO_DeInit(GPIOB, GPIO_PIN_10);

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    /* Peripheral clock disable */
    __HAL_RCC_I2C3_CLK_DISABLE();

    /**I2C3 GPIO Configuration
    PA8     ------> I2C3_SCL
    PB4     ------> I2C3_SDA
    */
    HAL_GPIO_DeInit(GPIOA, GPIO_PIN_8);

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    __HAL_RCC_SPI1_CLK_ENABLE();

    __HAL_RCC_GPIOA_CLK_ENABLE();
    /**SPI1 GPIO Configuration
    PA5     ------> SPI1_SCK
    PA6     ------> SPI1_MISO
    PA7     ------> SPI1_MOSI
    PA15     ------> SPI1_NSS
    */
    GPIO_InitStruct.Pin = GPIO_PIN_5|GPIO_PIN_6|GPIO_PIN_7|GPIO_PIN_15;
    GPIO_InitStruct.Mode = GPIO_MODE_AF_PP;
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    /* Peripheral clock disable */
    __HAL_RCC_SPI1_CLK_DISABLE();

    /**SPI1 GPIO Configuration
    PA5     ------> SPI1_SCK
    PA6     ------> SPI1_MISO
    PA7     ------> SPI1_MOSI
    PA15     ------> SPI1_NSS
    */
    HAL_GPIO_DeInit(GPIOA, GPIO_PIN_5|GPIO_PIN_6|GPIO_PIN_7|GPIO_PIN_15);

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
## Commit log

2023-04-25 Initial schematic and BOM
    Just the microprocessor on this initial version
2023-04-25 Initial CubeIDE files
2023-04-26 Updated schematic
    First rev of complete CPU board schematic
2023-04-27 Complete CPU board
2023-04-29 Reorganize KiCad Directory
    Create separate directories for development boards
2023-05-01 Added SX1262 Symbol
2023-05-01 Update SX1262 Symbol
2023-05-01 Update LoRa Board Schematic
2023-05-02 Completed schematic for LoRa board
2023-05-03 Completed design and BOM
2023-05-03 Changed RF switch on LoRa board
    Based on parts availability
2023-05-06 Updated USB Connector
2023-05-06 Update CubeIDE
2023-05-06 Eagle PCB files created
    Schematic and board layout
2023-05-06 LoRa Silkscreen
    Silkscreen and gerber files added
2023-05-20 Gerber and Fab Files created
    silkscreen and origin modified
2023-05-20 BOM update
2023-05-24 Updated BOM and added DFM analysis
2023-06-12 Blinking LED achieved
2023-06-12 CPU CPL edit
    rotate reset switch
2023-06-13 USB communications and documentation updates
2023-06-13 Updated documentation
2023-06-14 Update processor config to talk to LoRa board
2023-06-14 Added empty SX1262 driver files
2023-06-14 Initial SX1262 driver functions
2023-06-16 Initial SPI communication working
2023-06-16 Typos corrected
2023-06-17 Updated CPU schematic for 14 pin debug connector
2023-06-17 Updated backup
2023-06-19 Added functionality to the LoRa driver
2023-06-20 Initial SX1262 driver working
2023-06-20 Updated debugging document
2023-06-21 Experimenting with RF Output
2023-06-22 Updated proto test doc
2023-06-22 RF power measurments
2023-06-23 Initial documentation for LoRa gateway
2023-06-23 Updated Prototype debugging.md
2023-06-23 Gateway initial receive test
2023-06-27 Linked documentation together
2023-06-28 CPU revB
    Added CPU revB Eagle, gerber, BOM, and CPL files.
2023-06-28 Working on Transmit/Receive
2023-06-28 LoRa transmission working
2023-06-29 Transmit test refined
2023-06-29 Initial receive code
2023-06-30 CPU revB.2
    Decreased width on CPU board to 1 inch. Rearranged edge pins.
2023-06-30 Receive functionality verified
2023-07-03 Update docs and back to transmit test
2023-07-03 Reorganized documentation
2023-07-03 Add CPU Rev B.2 documentation
2023-07-03 Improved signal strength display
2023-07-07 Back to the blinking light to test Rev B.2
2023-07-10 Update task list
2023-07-11 Added range testing
2023-07-12 Update checklist
2023-07-12 Added USART3 to config
    For testing one wire interface
2023-07-12 Added sensor module architecture document
2023-07-13 Added GPIO for one wire interface
2023-07-13 Outline for combined board schematics
2023-07-17 Started Central Subsystem
2023-07-18 Examined CPU clock configuration
2023-07-20 Successfully tested module ID circuit
2023-07-24 Central subsystem design
2023-07-25 ID circuit working with buffer
2023-07-25 Documented ID circuit working
2023-07-27 Added FET to switch sensor power
2023-07-28 Added solar charging circuit
2023-07-31 Further work on power subsystem
2023-07-31 More work on power subsystem
2023-08-01 Further progress on power subsystem
2023-08-01 Development version of power subsystem
2023-08-04 Power Subsystem Development PCB
    Added Power Development Board PCB layout, BOM, and CPL files
2023-08-05 Power PCB
    added mounting holes
2023-08-05 Power A.2
    Added connector for battery
2023-08-07 Power Board revision
    Fixed error on MOSFET footprint and adjusted battery connector position in CPL file
2023-08-07 Power JLC Gerber update
    corrected version
2023-08-11 Added sensor subsystem project
2023-08-11 Sensor subsystem processor research
2023-08-24 Added Arduino IDE documentation
2023-08-25 No changes
2023-09-12 Update Voltage_and_current_meter.ino
    Measure both battery and panel
2023-09-13 test rig working with logging
2023-09-14 Power Dev. revA.3
    Revised error on Power Board Q1/Q2 - swapped D/S pins. Updated JLC order folder
2023-09-16 Drive LEDs from the processor
2023-09-16 Added power development board DFM
2023-09-18 Add deep sleep
2023-09-19 Update task list (Tasks.md)
2023-09-19 Updated combined board schematics
2023-09-20 Updated combined board schematic
2023-09-20 Export combined board schematic to PDF
2023-09-21 Include UART pins
2023-09-21 Update UART pin labels
2023-09-21 Updated schematic PDF
2023-09-25 Refined combined board design
2023-09-26 Clean up schematic
2023-09-27 Added CAD model for PCB size
2023-09-28 Combined Board Layout
    Comstation revA.1
2023-10-01 Comstation JLC files
2023-10-02 Changed a couple of parts
2023-10-02 Comstation revA.1 error fix
    fixed Y1 footprint
2023-10-02 Update BOM for Comstation board
2023-10-04 Update BOM based on JLCPCB review
2023-10-11 Update DFM
2023-10-16 Update tasks checklist
2023-10-16 Enable SubGhz interface
2023-10-17 Working on LoRa SPI interface
2023-10-19 SPI to LoRa transceiver working
2023-11-17 Update automated backup files
2023-11-17 Test that debugging still working

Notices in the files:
Software/CubeIDE/Sensor subsystem/Core/Src/stm32l0xx_hal_msp.c:
Copyright (c) 2023 STMicroelectronics.
All rights reserved.
This software is licensed under terms that can be found in the LICENSE file
